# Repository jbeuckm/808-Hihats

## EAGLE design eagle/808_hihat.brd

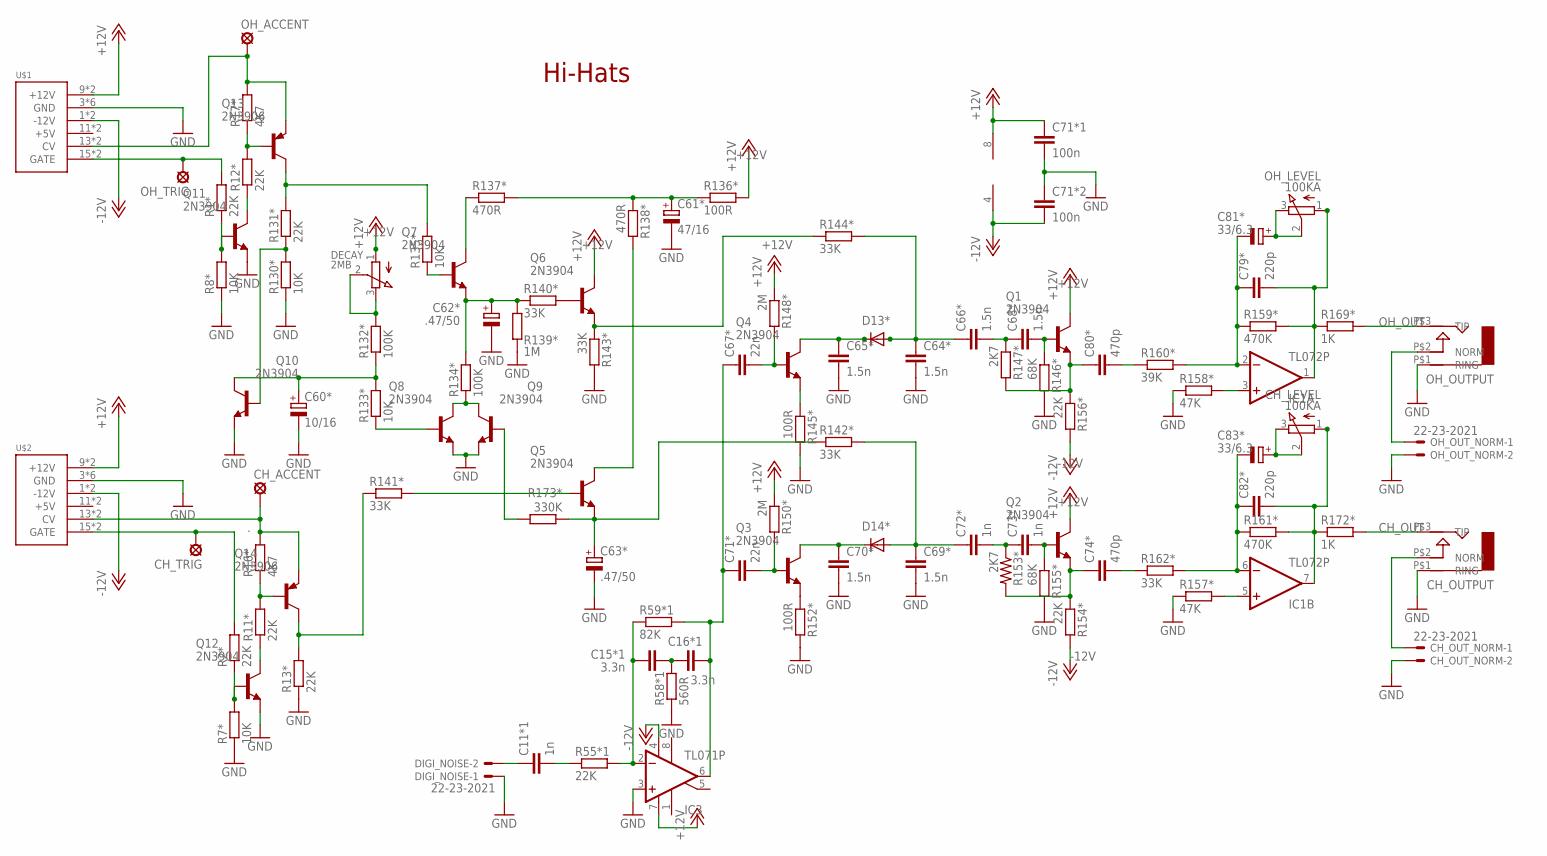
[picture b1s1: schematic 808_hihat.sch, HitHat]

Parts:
C11*1: 1n; C035-025X75
C15*1: 3.3n; C050-024X044
C16*1: 3.3n; C035-025X75
C60*: 10/16; E2,5-5
C61*: 47/16; E2,5-5
C62*, C63*: .47/50; E2,5-5
C64*, C66*, C69*: 1.5n; C050-024X044
C65*, C70*: 1.5n; C035-025X75
C67*: 22n; C050-024X044
C68*: 1.5n; C050-025X075
C71*: 22n; C035-030X60
C71*1: 100n; C050-024X044
C71*2: 100n; C030-025X75
C72*, C73*: 1n; C050-024X044
C74*: 470p; C050-025X075
C79*, C82*: 220p; C025-025X050
C80*: 470p; C050-024X044
C81*: 33/6.3; E3,5-8
C83*: 33/6.3; E2-5
CH_ACCENT: LSP11
CH_LEVEL: 100KA; 3RP/1610N
CH_OUTPUT: AUDIO-JACK; ERTHENVAR-JACK-90DEG
CH_OUT_NORM: 22-23-2021
CH_TRIG: LSP11
D13*, D14*: 1N4148DO35-10; DO35-10
DECAY: 2MB; 3RP/1610N
DIGI_NOISE: 22-23-2021
IC1: TL072P; DIL08
IC3: TL071P; DIL08
OH_ACCENT: LSP11
OH_LEVEL: 100KA; 3RP/1610N
OH_OUTPUT: AUDIO-JACK; ERTHENVAR-JACK-90DEG
OH_OUT_NORM: 22-23-2021
OH_TRIG: LSP11
Q1, Q2, Q3, Q4, Q5, Q6, Q7, Q8, Q9, Q10, Q11, Q12: 2N3904; TO92
Q13, Q14: 2N3906; TO92
R1*: 22K; 0207/2V
R2*, R13*, R55*1, R131*, R154*: 22K; 0207/5V
R7*, R8*: 10K; 0207/5V
R11*, R12*, R156*: 22K; 0207/7
R16*, R17*: 4K7; 0207/5V
R58*1: 560R; 0207/5V
R59*1: 82K; 0207/7
R130*, R133*, R135*: 10K; 0207/7
R132*: 100K; 0207/5V
R134*: 100K; 0207/7
R136*, R145*, R152*: 100R; 0207/5V
R137*, R138*: 470R; 0207/5V
R139*: 1M; 0207/5V
R140*, R162*: 33K; 0207/7
R141*, R142*, R143*, R144*: 33K; 0207/5V
R146*, R155*: 68K; 0207/7
R147*: 2K7; 0309/10
R148*, R150*: 2M; 0207/5V
R153*: 2K7; 0207/5V
R157*, R158*: 47K; 0207/7
R159*, R161*: 470K; 0207/2V
R160*: 39K; 0207/7
R169*: 1K; 0207/7
R172*: 1K; 0207/5V
R173*: 330K; 0207/7
U$1, U$2: POWER; POWER_16

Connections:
+12V: C71*1.1, DECAY.1 (A), IC1.8 (V+), IC3.7 (V+), Q1.1 (C), Q2.1 (C), Q6.1 (C), R136*.2, R148*.1, R150*.1, U$1.9 (+12V), U$1.10 (+12V), U$2.9 (+12V), U$2.10 (+12V)
-12V: C71*2.P$2 (2), IC1.4 (V-), IC3.4 (V-), R154*.2, R156*.2, U$1.1 (-12V), U$1.2 (-12V), U$2.1 (-12V), U$2.2 (-12V)
.: CH_ACCENT.MP, Q14.3 (E), R16*.2, U$2.13 (CV), U$2.14 (CV)
CH_OUT: CH_OUTPUT.P$3 (TIP), R172*.2
GND: C60*.-, C61*.-, C62*.-, C63*.-, C64*.2, C65*.P$2 (2), C69*.2, C70*.P$2 (2), C71*1.2, C71*2.P$1 (1), CH_OUTPUT.P$1 (RING), CH_OUT_NORM.2, DIGI_NOISE.1, IC3.3 (+IN), OH_OUTPUT.P$1 (RING), OH_OUT_NORM.2, Q8.3 (E), Q9.3 (E), Q10.3 (E), Q11.3 (E), Q12.3 (E), R7*.1, R8*.1, R13*.1, R58*1.1, R130*.1, R139*.2, R143*.2, R145*.2, R146*.2, R152*.2, R155*.2, R157*.1, R158*.1, U$1.3 (GND), U$1.4 (GND), U$1.5 (GND), U$1.6 (GND), U$1.7 (GND), U$1.8 (GND), U$2.3 (GND), U$2.4 (GND), U$2.5 (GND), U$2.6 (GND), U$2.7 (GND), U$2.8 (GND)
unnamed: DECAY.2 (S), DECAY.3 (E), R132*.2
unnamed: C11*1.P$1 (1), DIGI_NOISE.2
unnamed: C11*1.P$2 (2), R55*1.1
unnamed: C15*1.1, IC3.2 (-IN), R55*1.2, R59*1.1
unnamed: C15*1.2, C16*1.P$1 (1), R58*1.2
unnamed: Q6.2 (B), R140*.2
unnamed: Q4.3 (E), R145*.1
unnamed: Q3.3 (E), R152*.1
unnamed: OH_OUTPUT.P$2 (NORM), OH_OUT_NORM.1
unnamed: CH_OUTPUT.P$2 (NORM), CH_OUT_NORM.1
unnamed: OH_ACCENT.MP, Q13.3 (E), R17*.2, U$1.13 (CV), U$1.14 (CV)
unnamed: OH_TRIG.MP, R1*.2, U$1.15 (GATE), U$1.16 (GATE)
unnamed: IC1.3 (+IN), R158*.2
unnamed: IC1.5 (+IN), R157*.2
unnamed: CH_TRIG.MP, R2*.2, U$2.15 (GATE), U$2.16 (GATE)
unnamed: C81*.+, OH_LEVEL.2 (S), OH_LEVEL.3 (E)
unnamed: C64*.1, C66*.1, D13*.A, R144*.2
unnamed: C69*.1, C72*.1, D14*.A, R142*.2
unnamed: C83*.+, CH_LEVEL.2 (S), CH_LEVEL.3 (E)
unnamed: Q12.2 (B), R2*.1, R7*.2
unnamed: Q14.2 (B), R11*.2, R16*.1
unnamed: Q12.1 (C), R11*.1
unnamed: Q14.1 (C), R13*.2, R141*.1
unnamed: Q11.2 (B), R1*.1, R8*.2
unnamed: Q13.2 (B), R12*.2, R17*.1
unnamed: Q11.1 (C), R12*.1
unnamed: Q13.1 (C), R131*.2, R135*.2
unnamed: Q7.1 (C), R137*.1
unnamed: Q7.2 (B), R135*.1
unnamed: C62*.+, Q7.3 (E), R134*.2, R139*.1, R140*.1
unnamed: Q8.1 (C), Q9.1 (C), R134*.1
unnamed: Q8.2 (B), R133*.1
unnamed: C60*.+, Q10.1 (C), R132*.1, R133*.2
unnamed: C61*.+, R136*.1, R137*.2, R138*.1
unnamed: Q5.2 (B), R141*.2
unnamed: Q5.1 (C), R138*.2
unnamed: Q9.2 (B), R173*.2
unnamed: C63*.+, Q5.3 (E), R142*.1, R173*.1
unnamed: Q6.3 (E), R143*.1, R144*.1
unnamed: C71*.P$2 (2), Q3.2 (B), R150*.2
unnamed: C67*.2, Q4.2 (B), R148*.2
unnamed: C70*.P$1 (1), D14*.C, Q3.1 (C)
unnamed: C65*.P$1 (1), D13*.C, Q4.1 (C)
unnamed: C66*.2, C68*.1, R147*.1
unnamed: C72*.2, C73*.1, R153*.1
unnamed: C68*.2, Q1.2 (B), R146*.1
unnamed: C73*.2, Q2.2 (B), R155*.1
unnamed: C74*.2, R162*.1
unnamed: C80*.2, R160*.1
unnamed: C79*.1, C81*.-, IC1.2 (-IN), R159*.1, R160*.2
unnamed: C79*.2, IC1.1 (OUT), OH_LEVEL.1 (A), R159*.2, R169*.1
unnamed: C82*.1, C83*.-, IC1.6 (-IN), R161*.1, R162*.2
unnamed: C82*.2, CH_LEVEL.1 (A), IC1.7 (OUT), R161*.2, R172*.1
unnamed: Q10.2 (B), R130*.2, R131*.1
unnamed: C80*.1, Q1.3 (E), R147*.2, R156*.1
unnamed: C74*.1, Q2.3 (E), R153*.2, R154*.1
OH_OUT: OH_OUTPUT.P$3 (TIP), R169*.2
TO_HH: C16*1.P$2 (2), C67*.1, C71*.P$1 (1), IC3.6 (OUT), R59*1.2

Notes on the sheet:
Hi-Hats

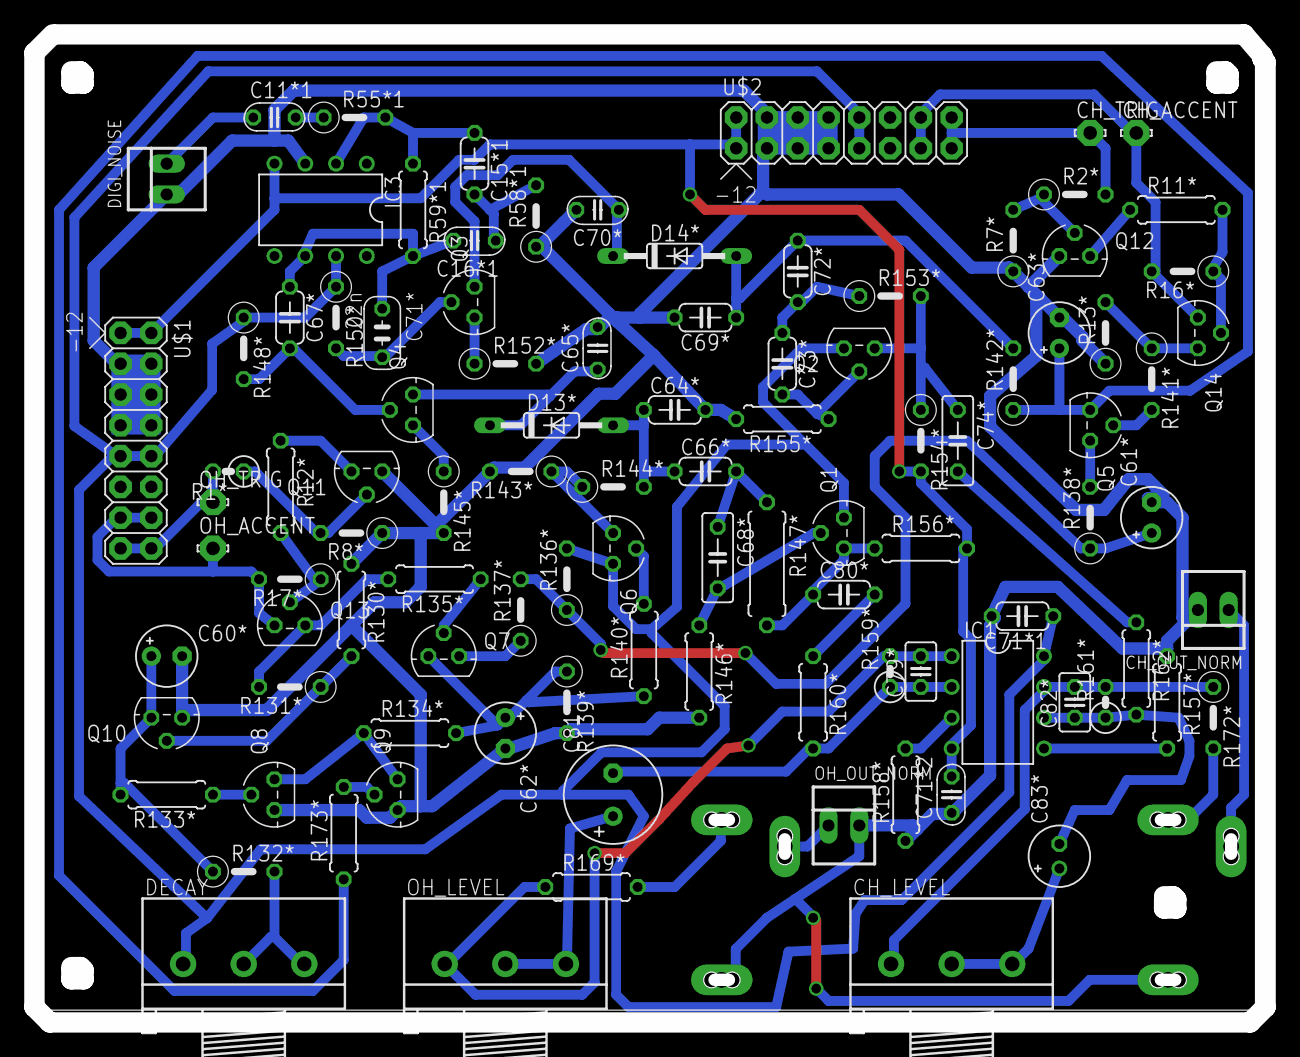
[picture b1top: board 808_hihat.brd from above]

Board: 2 copper layers, 101.6 x 81.5 mm, 103 parts (0 on the bottom side), 63 nets.

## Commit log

2015-01-19 schematic is ready
2015-01-22 redoing board by hand from schematic
2015-01-22 manual placement goes on
2015-01-23 manual placement first draft
2015-01-23 baby steps
2015-01-23 closer
2015-01-24 three routes left
2015-01-24 routed but rough
2015-01-24 labeled the transistor values
2015-01-24 ready for a test run on the cnc
2015-01-29 hihats work, adding a panel
2016-05-12 replaced parts
2016-05-12 checked with 808 manual
2016-05-12 board with drc
2016-05-13 beginning manual layout
2016-05-13 parts on the board
2016-05-13 93pct ar
2016-05-13 94pct ar
2016-05-15 94pct6 ar
2016-05-15 rotated output amp looks promising
2016-05-15 95pct5 ar
2016-05-15 routed
2016-05-15 cutout
2016-05-25 working
